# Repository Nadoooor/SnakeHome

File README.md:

# SnakeHome

------------

------------

## Description:
SnakeHome is a local-hosted powerful Snake-Styled automation system, based on HAOS and using wireless relays and some sensors. Hosted on a Raspi 4 and directly driving I2C sensors and Digital sensors, using the Raspi's GPIO.

## Why I'm making this?
I like that I can automate and smartly control my whole house, and also using my voice to control it.
So, decided to make this project as i can host, control, automate, and integerate many things.

## Highlight:
* Snake-Styled Case
* Using I2C bus on the same Pi 4
* Has additional I2C buses using an I2C multiplexer
* Custom Pi Hat for the I2C buses, RGB strip, and Motion sensors.

## Some Photos:

### PCB:

### Schematic:

### 3D Case & Assembly:

> [!NOTE]
> Here you are the [Fusion Assembly Link](https://a360.co/44hYKPn)

## Bill of Materials:

| Item Name                                                                | Purchase Link                                                                                                                                                                                                      | Quantity | Price per Unit |                        Total |
| ------------------------------------------------------------------------ | ------------------------------------------------------------------------------------------------------------------------------------------------------------------------------------------------------------------ | -------: | -------------: | ---------------------------: |
| LCD HDMI 7 inch 800x480 Capacitive Touch Screen                          | [RAM-E Shop](https://www.ram-e-shop.com/shop/lcd-hdmi-7-lcd-hdmi-7-inch-800x480-capacitive-touch-screen-7048?srsltid=AfmBOorUe2tKtcn4JbvP1ZTpSPSQzv_4OBrRmaJJUFSKj4mR9VUcvmev)                                     |        1 |         $61.41 |                       $61.41 |
| Raspberry Pi 4                                                           | [Cytron](https://www.cytron.io/p-raspberry-pi-4-model-b-4gb?currency=USD&src=raspberrypi&__cf_chl_f_tk=1gVJC0yFA_oNHxKh2gmH2fEgdigKqShx7tK3YobdYoE-1783374661-1.0.1.1-hMaFJiEW5raPlFIFSo6CefCfJgAvDq53L9vreoigOKs) |        1 |           $100 |                         $100 |
| 4-Channel Wireless Relay Module ESP-12F (RM4W)                           | [Fares PCB](https://fares-pcb.com/product/4-channel-wireless-relay-module-esp-12f-rm4w/)                                                                                                                           |        5 |          $6.14 |                       $30.71 |
| AM-2320 Temperature & Humidity                                           | [RAM-E Shop](https://www.ram-e-shop.com/shop/sen-am2320-am-2320-temperature-humidity-calibrated-sensor-asair-r-original-brand-7776)                                                                                |        4 |          $3.58 |                       $14.32 |
| PIR Motion Sensor Module HC-SR501                                        | [RAM-E Shop](https://www.ram-e-shop.com/shop/kit-pir-module-pir-motion-sensor-module-hc-sr501-6673?srsltid=AfmBOooSD9HVb-FVRD6JP8KHQoaQlhenYvKXd5C95F_AjBWc5ugerphb)                                               |        2 |          $1.02 |                        $2.04 |
| TCA9548APWR I2C 8 channels bus multiplexer TSSOP24                       | [UGE-One](https://uge-one.com/product/tca9548apwr-i2c-8-channels-bus-multiplexer-tssop24/?srsltid=AfmBOooYz3AQkDL3NkKblc4A5gbOHgHDWNGNuuuX1uyoCiN8VXJXbU7l)                                                        |        1 |          $1.74 |                        $1.74 |
| Chip Resistor SMD 10Ω ±1% 62.5mW ±100ppm/℃ 0402                          | [Maker's Electronics](https://makerselectronics.com/product/chip-resistor-smd-10%cf%89-%c2%b11-62-5mw-%c2%b1100ppm-%e2%84%83-0402/)                                                                                |       11 |         $0.002 |                       $0.022 |
| B4B-XH-A JST XH Data Terminal Male 4 Pin Connector Header 2.5mm          | [Maker's Electronics](https://makerselectronics.com/product/b4b-xh-a-jst-xh-4-pin-header-2-5mm/)                                                                                                                   |        5 |         $0.012 |                        $0.06 |
| B3B-XH-A JST XH Data Terminal Male 3 Pin Connector Header 2.5mm          | [Maker's Electronics](https://makerselectronics.com/product/b3b-xh-a-jst-xh-3-pin-header-2-5mm/)                                                                                                                   |        2 |          $0.01 |                        $0.02 |
| Data Cable JST 3 Pin 2.54mm 26AWG 25cm One Side Terminal                 | [Maker's Electronics](https://makerselectronics.com/product/data-cable-3-pin-25cm-one-side/)                                                                                                                       |        2 |          $0.17 |                        $0.34 |
| PHR-4 JST PH Connector Housing Female 4 Pin 2mm with 20cm Terminal Cable | [Maker's Electronics](https://makerselectronics.com/product/phr-4-jst-ph-housing-4-2mm-20cm-cable/)                                                                                                                |        5 |          $0.10 |                        $0.50 |
| PCB (JLCPCB)                                                             | [JLCPCB Cart](https://cart.jlcpcb.com/)                                                                                                                                                                            |        5 |          $0.40 |                        $2.00 |
| E-POST (JLCPCB)                                                          | [JLCPCB Cart](https://cart.jlcpcb.com/)                                                                                                                                                                            |        1 |         $13.60 |                       $13.60 |
| 3D Prints                                                                | Local Vendor (Printfy-eg)                                                                                                                                                                                          |        1 |         $33.80 |                       $33.80 |
| NeoPixel Stick 8-bit WS2812 5050 RGB LED Driver Development Board        | [RAM-E Shop](https://www.ram-e-shop.com/shop/kit-ws2812-8-5050-strip-neopixel-stick-8-bit-ws2812-5050-rgb-led-driver-development-board-8257?srsltid=AfmBOoq2-D_xbTO2GzUTi27TZwHegidSzl2b0Z84DDxABTQgCfJVlCOd)      |        3 |          $1.00 |                        $3.00 |
| M3 & M2 Screws                                                           | [UGE-One Search](https://uge-one.com/?product_cat=&s=M3+screw&post_type=product)                                                                                                                                   |       18 |          $0.05 |                        $1.00 |
| M3 & M2 Inserts                                                          | [UGE-One Search](https://uge-one.com/?product_cat=&s=M3+screw&post_type=product)                                                                                                                                   |       18 |          $0.05 |                        $1.00 |
| USB Small Microphone | [Aliexpress](https://ar.aliexpress.com/item/1005005364449092.html?spm=a2g0o.productlist.main.3.5dff5b1cPDhfSt&algo_pvid=a4202c5b-f152-4748-b57b-737da53ad29c&algo_exp_id=a4202c5b-f152-4748-b57b-737da53ad29c-2&pdp_ext_f=%7B%22order%22%3A%22810%22%2C%22spu_best_type%22%3A%22price%22%2C%22eval%22%3A%221%22%2C%22fromPage%22%3A%22search%22%7D&pdp_npi=6%40dis%21EGP%21288.94%2153.27%21%21%215.37%210.99%21%402101590d17835041732383886e3d82%2112000032749797222%21sea%21EG%210%21ABX%211%210%21n_tag%3A-29910%3Bd%3A2e304f5e%3Bm03_new_user%3A-29895%3BpisId%3A5000000207410332&curPageLogUid=CMNS0Bh3jwOQ&utparam-url=scene%3Asearch%7Cquery_from%3A%7Cx_object_id%3A1005005364449092%7C_p_origin_prod%3A) | 1 | $1.00 | $1.00 |
| **TOTAL**                                                                | ~~                                                                                                                                                                                                                 |       ~~ |             ~~ | **$266.56 (THE PI IS HELL)** |

## How to Build:
1. Print the needed 3D parts and Pi hat.
2. Heat the inserts and put each one in its place.
3. Assemble the Pi4 and the Hat(After soldering it).
4. Place them inside the Case and use M3 screws to rainforce them.
6. Solder the 3 RGB Stick chain. 
5. Place the RGB Sticks and use M2 screws to rainforce them.
7. Connect the RGB sticks connector.
8. Connect the sensors connectors and take out each sensor wires from its hole.
9. Assemble the 3D Snake face parts and use Glue to rainforce them.
10. Assemble the Touch Screen using M3 screws in the Top Case.
11. Connect the Pis HDMI and USB to the screen. (The Screen will take its power from the USB as well as the Touch data.)
12. Place the Bottom Case on the wall and mark the Screw holes.
13. Make the holes in the wall and Place the 3D case on them.
14. Close the Top Case using M3 Screws.
15. Connect the Pi to Power and Lan cables.
16. Power on the Pi and use the [RasPi Imager](https://www.raspberrypi.com/software/) to Download and install the core Home assistant OS on your memory card.
17. Boot the Pi, and setup HAOS.
18. Enable the I2C bus using this [Method](https://www.abelectronics.co.uk/kb/article/1116/using-i2c-devices-with-home-assistant-on-the-raspberry-pi).
19. Use the [Configratino.yaml](Firmware/configuration.yaml) file to use the Sensors on the I2C bus, with the ESPHome integration in HAOS.
20. For the WiFi Relays, Flash the [Firmware Binary](Production/4ch_relays_BINs).
21. Connect it with HAOS as a ESPHome device.
22. Follow this [Tutorial](https://www.youtube.com/watch?v=XvbVePuP7NY) to integrate Voice assistant commands. (You can ignore the AI thingy)
23. Enjoy making automations and easy control over your house.

-------
# Made With ❤️, By Nadooor

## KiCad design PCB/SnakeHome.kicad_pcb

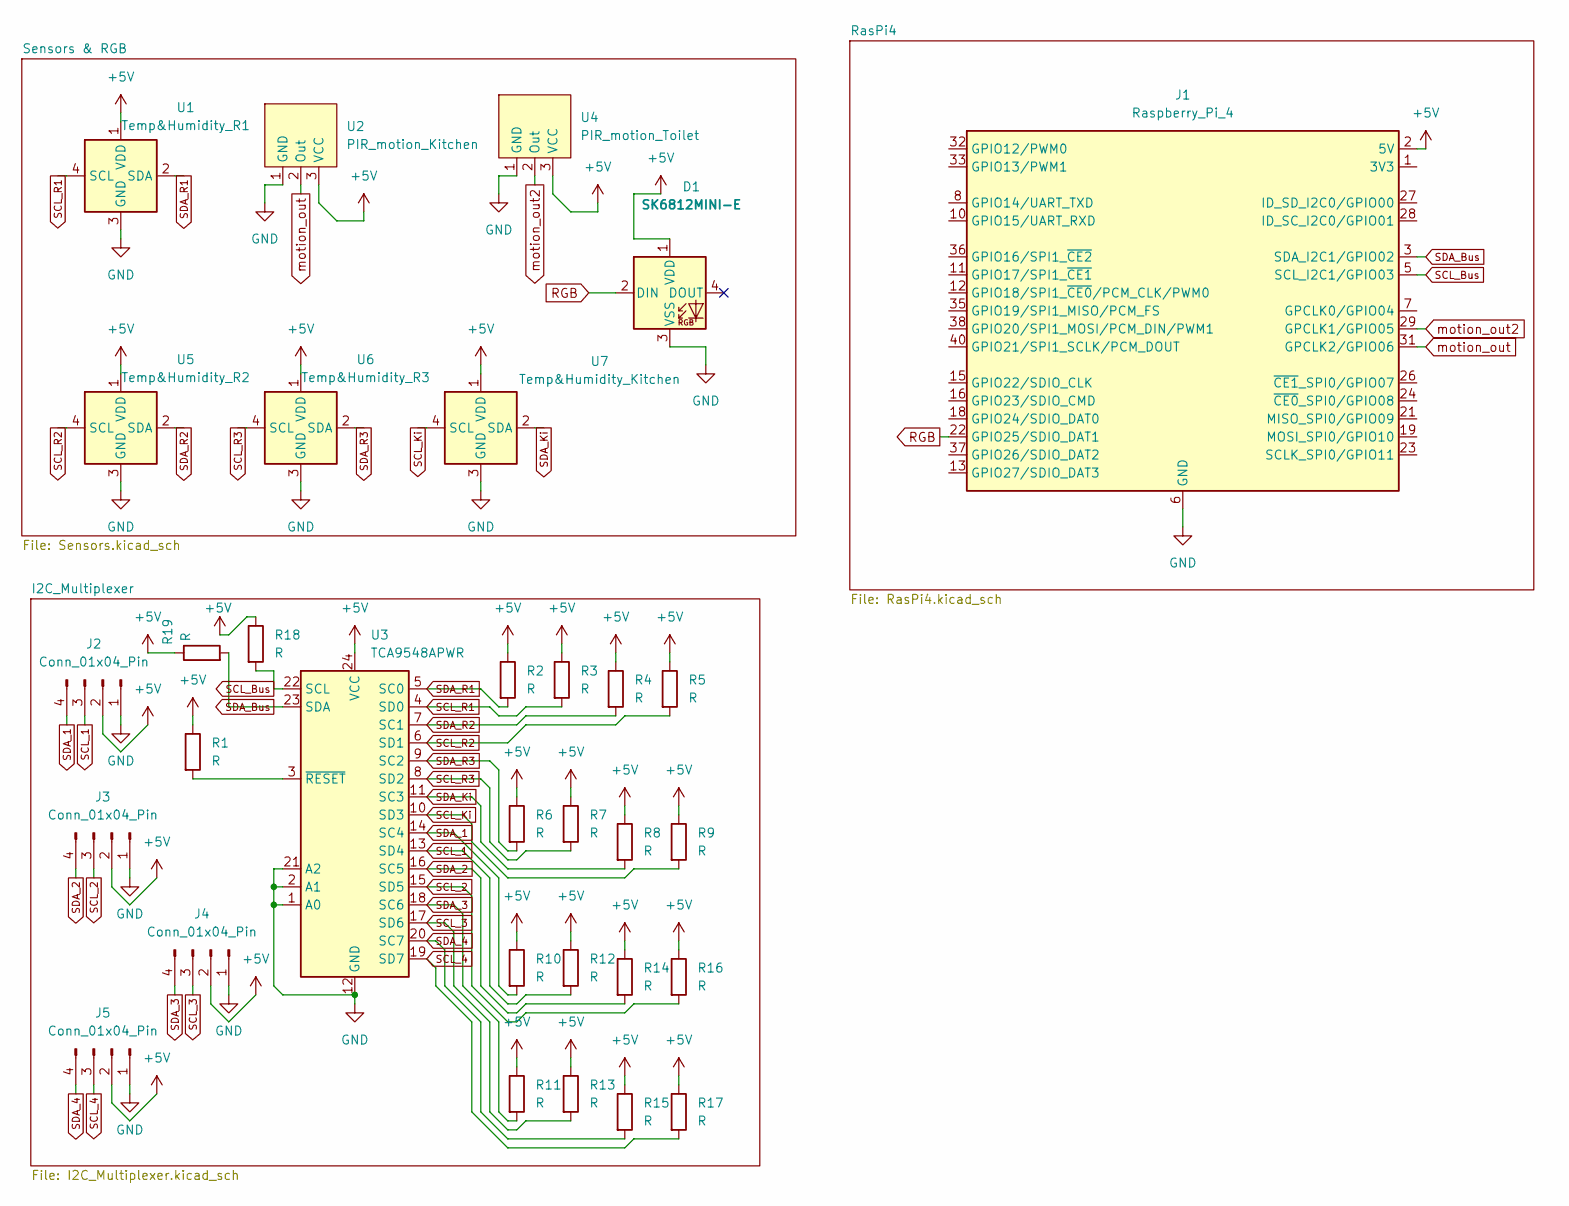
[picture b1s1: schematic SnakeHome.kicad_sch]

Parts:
D1: SK6812MINI-E; JST_XH_B3B-XH-A_1x03_P2.50mm_Vertical
J1: Raspberry_Pi_4; PinSocket_2x20_P2.54mm_Vertical
J2, J3, J4, J5: Conn_01x04_Pin; JST_XH_B4B-XH-A_1x04_P2.50mm_Vertical
R1, R2, R3, R4, R5, R6, R7, R8, R9, R10, R11, R12, R13, R14, R15, R16, R17, R18, R19: R; R_0402_1005Metric_Pad0.72x0.64mm_HandSolder
U1: Temp&Humidity_R1; JST_XH_B4B-XH-A_1x04_P2.50mm_Vertical
U2: PIR_motion_Kitchen; JST_XH_B3B-XH-A_1x03_P2.50mm_Vertical
U3: TCA9548APWR; TSSOP-24_4.4x7.8mm_P0.65mm
U4: PIR_motion_Toilet; JST_XH_B3B-XH-A_1x03_P2.50mm_Vertical
U5: Temp&Humidity_R2; JST_XH_B4B-XH-A_1x04_P2.50mm_Vertical
U6: Temp&Humidity_R3; JST_XH_B4B-XH-A_1x04_P2.50mm_Vertical
U7: Temp&Humidity_Kitchen; JST_XH_B4B-XH-A_1x04_P2.50mm_Vertical

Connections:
+5V: D1.1 (VDD), J1.2 (5V), J1.4 (5V), J2.2, J3.2, J4.2, J5.2, R1.1, R2.1, R3.1, R4.1, R5.1, R6.1, R7.1, R8.1, R9.1, R10.1, R11.1, R12.1, R13.1, R14.1, R15.1, R16.1, R17.1, R18.1, R19.1, U1.1 (VDD), U2.3 (VCC), U3.24 (VCC), U4.3 (VCC), U5.1 (VDD), U6.1 (VDD), U7.1 (VDD)
GND: D1.3 (VSS), J1.6 (GND), J1.9 (GND), J1.14 (GND), J1.20 (GND), J1.25 (GND), J1.30 (GND), J1.34 (GND), J1.39 (GND), J2.1, J3.1, J4.1, J5.1, U1.3 (GND), U2.1 (GND), U3.1 (A0), U3.2 (A1), U3.12 (GND), U3.21 (A2), U4.1 (GND), U5.3 (GND), U6.3 (GND), U7.3 (GND)
unnamed: J1.1 (3V3), J1.17 (3V3)
unnamed: R1.2, U3.3 (~RESET)
RGB: D1.2 (DIN), J1.22 (GPIO25/SDIO_DAT1)
SCL_1: J2.3, R12.2, U3.13 (SD4)
SCL_2: J3.3, R16.2, U3.15 (SD5)
SCL_3: J4.3, R13.2, U3.17 (SD6)
SCL_4: J5.3, R17.2, U3.19 (SD7)
SCL_Bus: J1.5 (SCL_I2C1/GPIO03), R18.2, U3.22 (SCL)
SCL_Ki: R9.2, U3.10 (SD3), U7.4 (SCL)
SCL_R1: R3.2, U1.4 (SCL), U3.4 (SD0)
SCL_R2: R5.2, U3.6 (SD1), U5.4 (SCL)
SCL_R3: R7.2, U3.8 (SD2), U6.4 (SCL)
SDA_1: J2.4, R10.2, U3.14 (SC4)
SDA_2: J3.4, R14.2, U3.16 (SC5)
SDA_3: J4.4, R11.2, U3.18 (SC6)
SDA_4: J5.4, R15.2, U3.20 (SC7)
SDA_Bus: J1.3 (SDA_I2C1/GPIO02), R19.2, U3.23 (SDA)
SDA_Ki: R8.2, U3.11 (SC3), U7.2 (SDA)
SDA_R1: R2.2, U1.2 (SDA), U3.5 (SC0)
SDA_R2: R4.2, U3.7 (SC1), U5.2 (SDA)
SDA_R3: R6.2, U3.9 (SC2), U6.2 (SDA)
motion_out: J1.31 (GPCLK2/GPIO06), U2.2 (Out)
motion_out2: J1.29 (GPCLK1/GPIO05), U4.2 (Out)

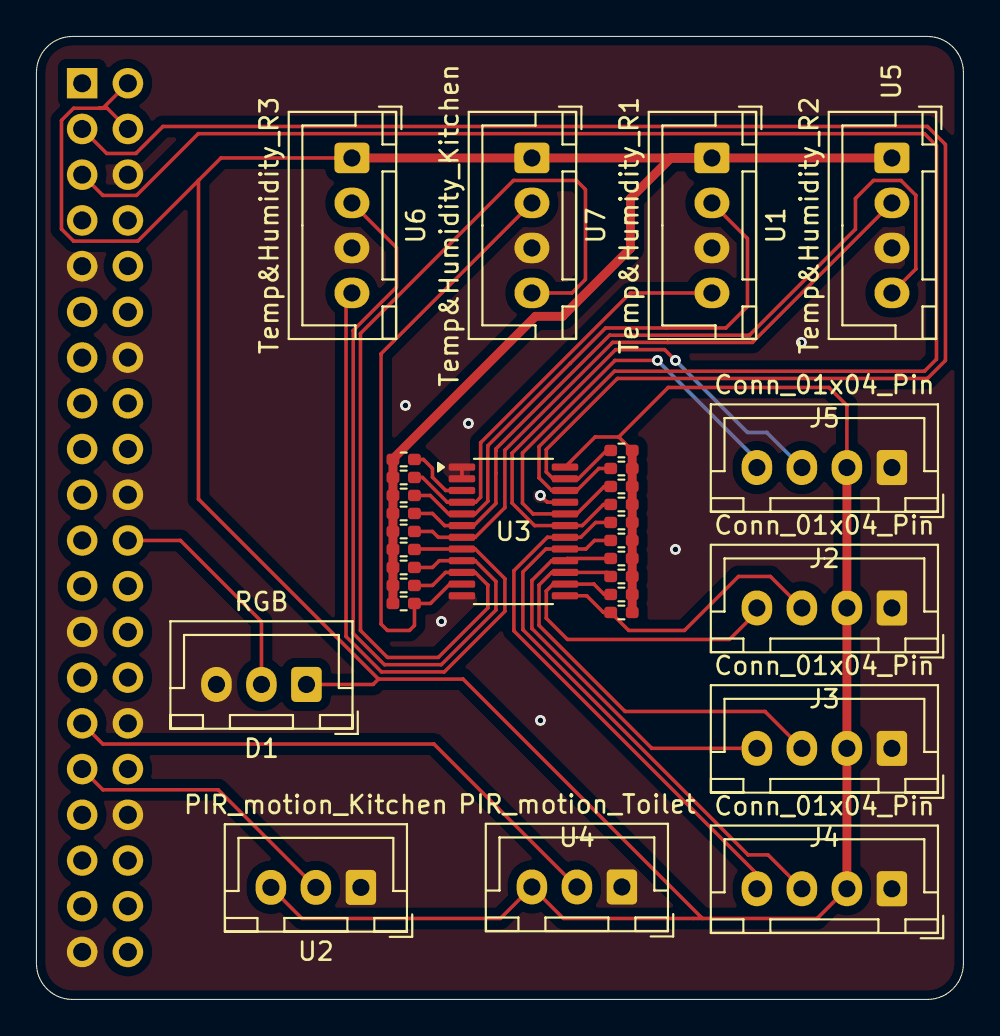
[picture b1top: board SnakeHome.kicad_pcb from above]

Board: 2 copper layers, 51.5 x 53.5 mm, 32 parts (1 on the bottom side), 25 nets.

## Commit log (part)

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2026-06-29 init the kicad project
2026-06-29 Made the schem, and thinking of what can i add
2026-06-30 Finished the PCB hat
